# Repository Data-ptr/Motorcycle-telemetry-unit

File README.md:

# Motorcycle-Telemetry-Unit
 MTU

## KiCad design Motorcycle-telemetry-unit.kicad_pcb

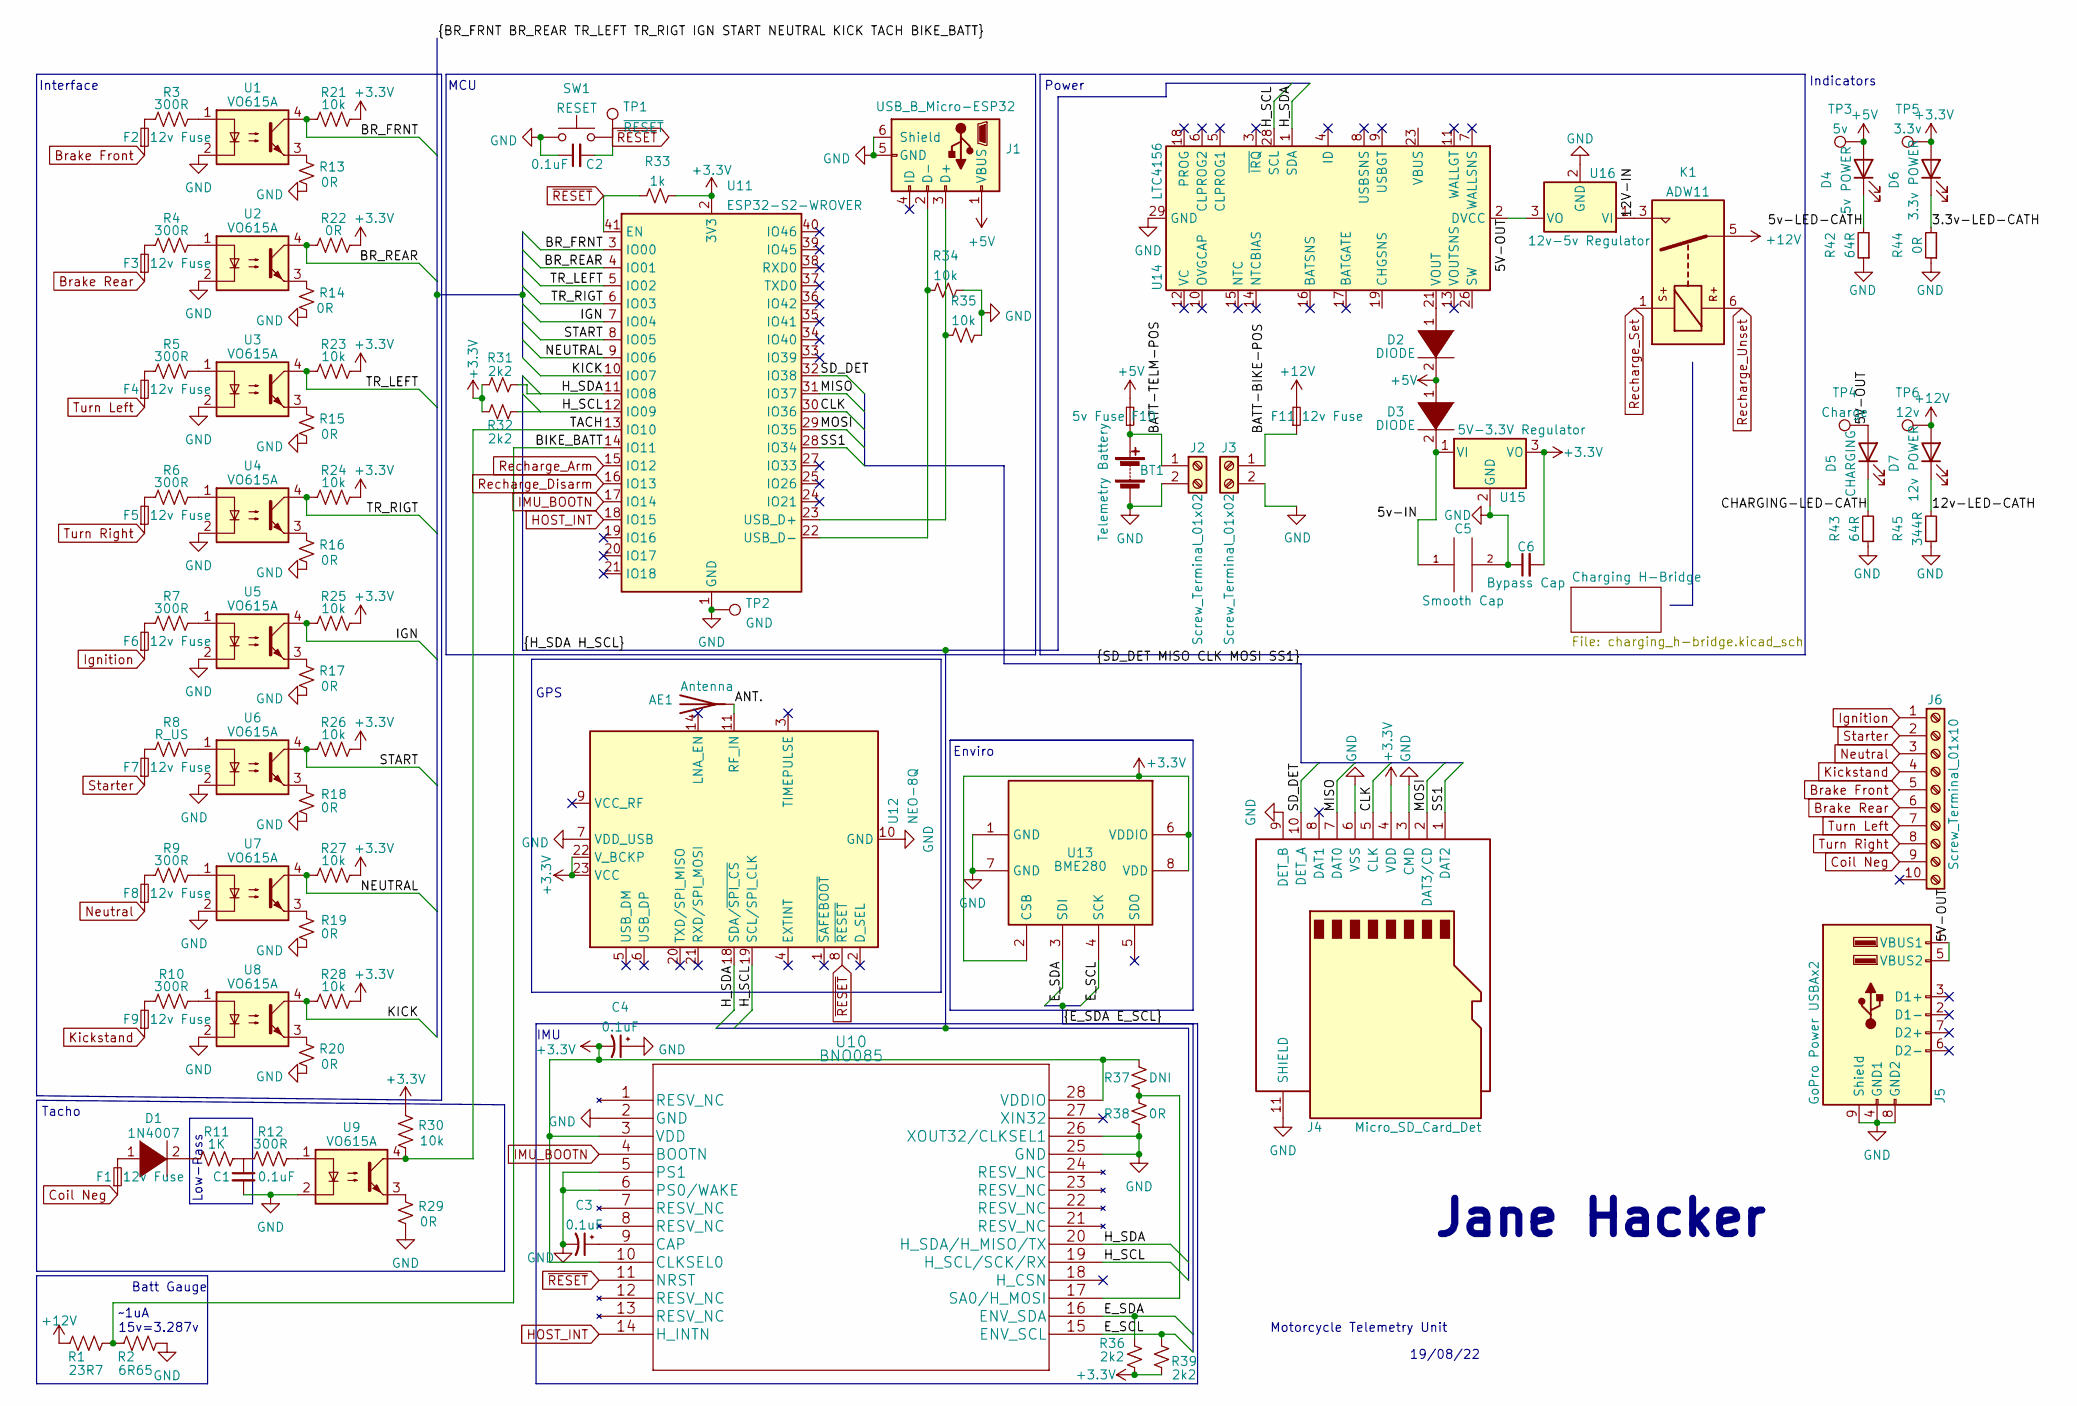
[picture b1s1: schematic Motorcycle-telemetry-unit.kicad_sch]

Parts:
AE1: Antenna; Texas_SWRA117D_2.4GHz_Right
BT1: Telemetry Battery; AMASS_XT60-M_1x02_P7.20mm_Vertical
C1, C2, C3, C4: 0.1uF; C_1206_3216Metric
C5: Smooth Cap; CP_Radial_D4.0mm_P1.50mm
C6: Bypass Cap; C_Disc_D3.0mm_W1.6mm_P2.50mm
D1: 1N4007; D_DO-35_SOD27_P7.62mm_Horizontal
D2, D3: DIODE; D_DO-35_SOD27_P7.62mm_Horizontal
D4: 5v POWER; LED_1206_3216Metric
D5: CHARGING; LED_1206_3216Metric
D6: 3.3v POWER; LED_1206_3216Metric
D7: 12v POWER; LED_1206_3216Metric
F1, F2, F3, F4, F5, F6, F7, F8, F9, F11: 12v Fuse; FUSE_BK-6013
F10: 5v Fuse; FUSE_BK-6013
J1: USB_B_Micro-ESP32; USB_Micro-B_Wuerth_629105150521
J2, J3: Screw_Terminal_01x02; TerminalBlock_Altech_AK300-2_P5.00mm
J4: Micro_SD_Card_Det; microSD_HC_Wuerth_693072010801
J5: GoPro Power USBAx2; USB_A_Wuerth_61400826021_Horizontal_Stacked
J6: Screw_Terminal_01x10; TerminalBlock_Phoenix_PT-1,5-10-5.0-H_1x10_P5.00mm_Horizont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
K1: ADW11; Relay_1P1T_NO_10x24x18.8mm_Panasonic_ADW11xxxxW_THT
R1: 23R7; R_1206_3216Metric
R2: 6R65; R_1206_3216Metric
R3, R4, R5, R6, R7, R9, R10, R12: 300R; R_1206_3216Metric
R8: R_US; R_1206_3216Metric
R11: 1K; R_1206_3216Metric
R13, R14, R15, R16, R17, R18, R19, R20, R22, R29, R38, R44: 0R; R_1206_3216Metric
R21, R23, R24, R25, R26, R27, R28, R30, R34, R35: 10k; R_1206_3216Metric
R31, R32, R36, R39: 2k2; R_1206_3216Metric
R33: 1k; R_1206_3216Metric
R37: DNI; R_1206_3216Metric
R42, R43: 64R; R_1206_3216Metric
R45: 344R; R_1206_3216Metric
SW1: RESET; SW_Push_1P1T_NO_6x6mm_H9.5mm
TP1: ~{RESET}; TestPoint_Loop_D2.50mm_Drill1.0mm
TP2: GND; TestPoint_Bridge_Pitch2.0mm_Drill0.7mm
TP3: 5v; TestPoint_Loop_D2.50mm_Drill1.0mm
TP4: Charge; TestPoint_Loop_D2.50mm_Drill1.0mm
TP5: 3.3v; TestPoint_Loop_D2.50mm_Drill1.0mm
TP6: 12v; TestPoint_Loop_D2.50mm_Drill1.0mm
U1, U2, U3, U4, U5, U6, U7, U8, U9: VO615A; DIP762W50P254L458H480Q4
U10: BNO085; LGA-28_5.2x3.8mm_P0.5mm
U11: ESP32-S2-WROVER
U12: NEO-8Q; ublox_NEO
U13: BME280; Bosch_LGA-8_2.5x2.5mm_P0.65mm_ClockwisePinNumbering
U14: LTC4156; QFN-28-1EP_4x5mm_P0.5mm_EP2.65x3.65mm
U15: 5V-3.3V Regulator; TO-252-2
U16: 12v-5v Regulator; TO-252-2

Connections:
+3V3: C4.2, C6.2, D6.2 (A), J4.4 (VDD), R21.2, R22.2, R23.2, R24.2, R25.2, R26.2, R27.2, R28.2, R30.2, R31.1, R32.1, R33.2, R36.1, R37.1, R39.1, TP5.1, U10.3 (VDD), U10.10 (CLKSEL0), U10.28 (VDDIO), U11.2 (3V3), U12.22 (V_BCKP), U12.23 (VCC), U13.2 (CSB), U13.6 (VDDIO), U13.8 (VDD), U15.3 (VO); also elsewhere on the board
+5V: D2.2 (A), D3.1 (K), D4.2 (A), F10.2, J1.1 (VBUS), TP3.1
+12V: D7.2 (A), F11.2, K1.5, R1.1, TP6.1
/3.3v-LED-CATH: D6.1 (K), R44.2
/5V-OUT: D5.2 (A), J5.1 (VBUS1), J5.5 (VBUS2), TP4.1, U14.2 (DVCC), U16.3 (VO)
/5v-IN: C5.1, D3.2 (A), U15.1 (VI)
/5v-LED-CATH: D4.1 (K), R42.2
/12V-IN: K1.3, U16.1 (VI)
/12v-LED-CATH: D7.1 (K), R45.2
/ANT.: AE1.1 (A), U12.11 (RF_IN)
/BATT-BIKE-POS: F11.1, J3.1
/BATT-TELM-POS: BT1.1 (+), F10.1, J2.1
/BIKE_BATT: R1.2, R2.1, U11.14 (IO11)
/BR_FRNT: R21.1, U1.4, U11.3 (IO00)
/BR_REAR: R22.1, U2.4, U11.4 (IO01)
/CHARGING-LED-CATH: D5.1 (K), R43.2
/CLK: J4.5 (CLK), U11.30 (IO36)
/E_SCL: R39.2, U10.15 (ENV_SCL), U13.4 (SCK)
/E_SDA: R36.2, U10.16 (ENV_SDA), U13.3 (SDI)
/H_SCL: R32.2, U10.19 (H_SCL/SCK/RX), U11.12 (IO09), U12.19 (SCL/SPI_CLK), U14.28 (SCL)
/H_SDA: R31.2, U10.20 (H_SDA/H_MISO/TX), U11.11 (IO08), U12.18 (SDA/~SPI_CS), U14.1 (SDA)
/IGN: R25.1, U5.4, U11.7 (IO04)
/KICK: R28.1, U8.4, U11.10 (IO07)
/MISO: J4.7 (DAT0), U11.31 (IO37)
/MOSI: J4.2 (DAT3/CD), U11.29 (IO35)
/NEUTRAL: R27.1, U7.4, U11.9 (IO06)
/SD_DET: J4.10 (DET_A), U11.32 (IO38)
/SS1: J4.1 (DAT2), U11.28 (IO34)
/START: R26.1, U6.4, U11.8 (IO05)
/TACH: R30.1, U9.4, U11.13 (IO10)
/TR_LEFT: R23.1, U3.4, U11.5 (IO02)
/TR_RIGT: R24.1, U4.4, U11.6 (IO03)
Brake Front: F2.1, J6.5
Brake Rear: F3.1, J6.6
Coil Neg: F1.1, J6.9
GND: BT1.2 (-), C1.2, C2.1, C3.2, C4.1, C5.2, C6.1, J1.5 (GND), J1.6 (Shield), J2.2, J3.2, J4.3 (CMD), J4.6 (VSS), J4.9 (DET_B), J4.11 (SHIELD), J5.4 (GND1), J5.8 (GND2), J5.9 (Shield), R2.2, R13.2, R14.2, R15.2, R16.2, R17.2, R18.2, R19.2, R20.2, R29.2, R34.2, R35.2, R38.2, R42.1, R43.1, R44.1, R45.1, SW1.1, TP2.1, U1.2, U2.2, U3.2, U4.2, U5.2, U6.2, U7.2, U8.2, U9.2, U10.2 (GND), U10.5 (PS1), U10.6 (PS0/WAKE), U10.25 (GND), U10.26 (XOUT32/CLKSEL1), U11.1 (GND), U11.26 (GND), U11.42 (GND), U11.43 (GND), U12.7 (VDD_USB), U12.10 (GND), U12.12 (GND), U12.13 (GND), U12.24 (GND), U13.1 (GND), U13.7 (GND), U14.29 (GND), U15.2 (GND), U16.2 (GND); also elsewhere on the board
HOST_INT: U10.14 (H_INTN), U11.18 (IO15)
IMU_BOOTN: U10.4 (BOOTN), U11.17 (IO14)
Ignition: F6.1, J6.1
Kickstand: F9.1, J6.4
unnamed: C1.1, R11.2, R12.1
unnamed: C3.1, U10.9 (CAP)
unnamed: D1.1 (K), F1.2
unnamed: D1.2 (A), R11.1
unnamed: D2.1 (K), U14.21 (VOUT), U14.22 (VOUT)
unnamed: F2.2, R3.1
unnamed: F3.2, R4.1
unnamed: F4.2, R5.1
unnamed: F5.2, R6.1
unnamed: F6.2, R7.1
unnamed: F7.2, R8.1
unnamed: F8.2, R9.1
unnamed: F9.2, R10.1
unnamed: J1.2 (D-), R34.1, U11.22 (USB_D-)
unnamed: J1.3 (D+), R35.1, U11.23 (USB_D+)
unnamed: R3.2, U1.1
unnamed: R4.2, U2.1
unnamed: R5.2, U3.1
unnamed: R6.2, U4.1
unnamed: R7.2, U5.1
unnamed: R8.2, U6.1
unnamed: R9.2, U7.1
unnamed: R10.2, U8.1
unnamed: R12.2, U9.1
unnamed: R13.1, U1.3
unnamed: R14.1, U2.3
unnamed: R15.1, U3.3
unnamed: R16.1, U4.3
unnamed: R17.1, U5.3
unnamed: R18.1, U6.3
unnamed: R19.1, U7.3
unnamed: R20.1, U8.3
unnamed: R29.1, U9.3
unnamed: R37.2, R38.1, U10.17 (SA0/H_MOSI)
unnamed: U14.19 (CHGSNS), U14.20 (CHGSNS)
unnamed: U14.23 (VBUS), U14.24 (VBUS), U14.25 (VBUS)
unnamed: U14.26 (SW), U14.27 (SW)
Neutral: F8.1, J6.3
Recharge_Arm: U11.15 (IO12); also elsewhere on the board
Recharge_Disarm: U11.16 (IO13); also elsewhere on the board
Recharge_Set: K1.1; also elsewhere on the board
Recharge_Unset: K1.6; also elsewhere on the board
Starter: F7.1, J6.2
Turn Left: F4.1, J6.7
Turn Right: F5.1, J6.8
~RESET: C2.2, R33.1, SW1.2, TP1.1, U10.11 (NRST), U11.41 (EN), U12.8 (~RESET)

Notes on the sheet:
MCU
Jane Hacker
Low-Pass
Interface
Power
Motorcycle Telemetry Unit
19/08/22
GPS
Enviro
Batt Gauge
Indicators
~1uA 15v=3.287v
IMU
Tacho

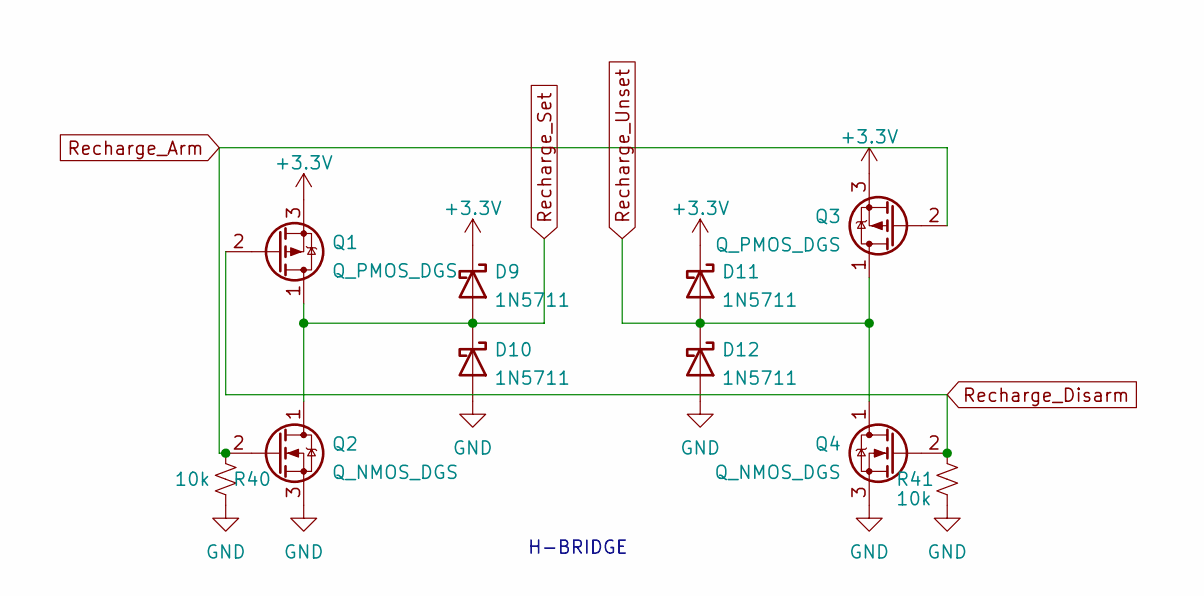
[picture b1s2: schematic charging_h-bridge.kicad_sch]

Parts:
D9, D10, D11, D12: 1N5711; D_DO-35_SOD27_P7.62mm_Horizontal
Q1, Q3: Q_PMOS_DGS; TO-220-3_Vertical
Q2, Q4: Q_NMOS_DGS; TO-220-3_Vertical
R40, R41: 10k; R_1206_3216Metric

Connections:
+3V3: D9.1 (K), D11.1 (K), Q1.3 (S), Q3.3 (S); also elsewhere on the board
GND: D10.2 (A), D12.2 (A), Q2.3 (S), Q4.3 (S), R40.1, R41.2; also elsewhere on the board
Recharge_Arm: Q2.2 (G), Q3.2 (G), R40.2; also elsewhere on the board
Recharge_Disarm: Q1.2 (G), Q4.2 (G), R41.1; also elsewhere on the board
Recharge_Set: D9.2 (A), D10.1 (K), Q1.1 (D), Q2.1 (D); also elsewhere on the board
Recharge_Unset: D11.2 (A), D12.1 (K), Q3.1 (D), Q4.1 (D); also elsewhere on the board

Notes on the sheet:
H-BRIDGE

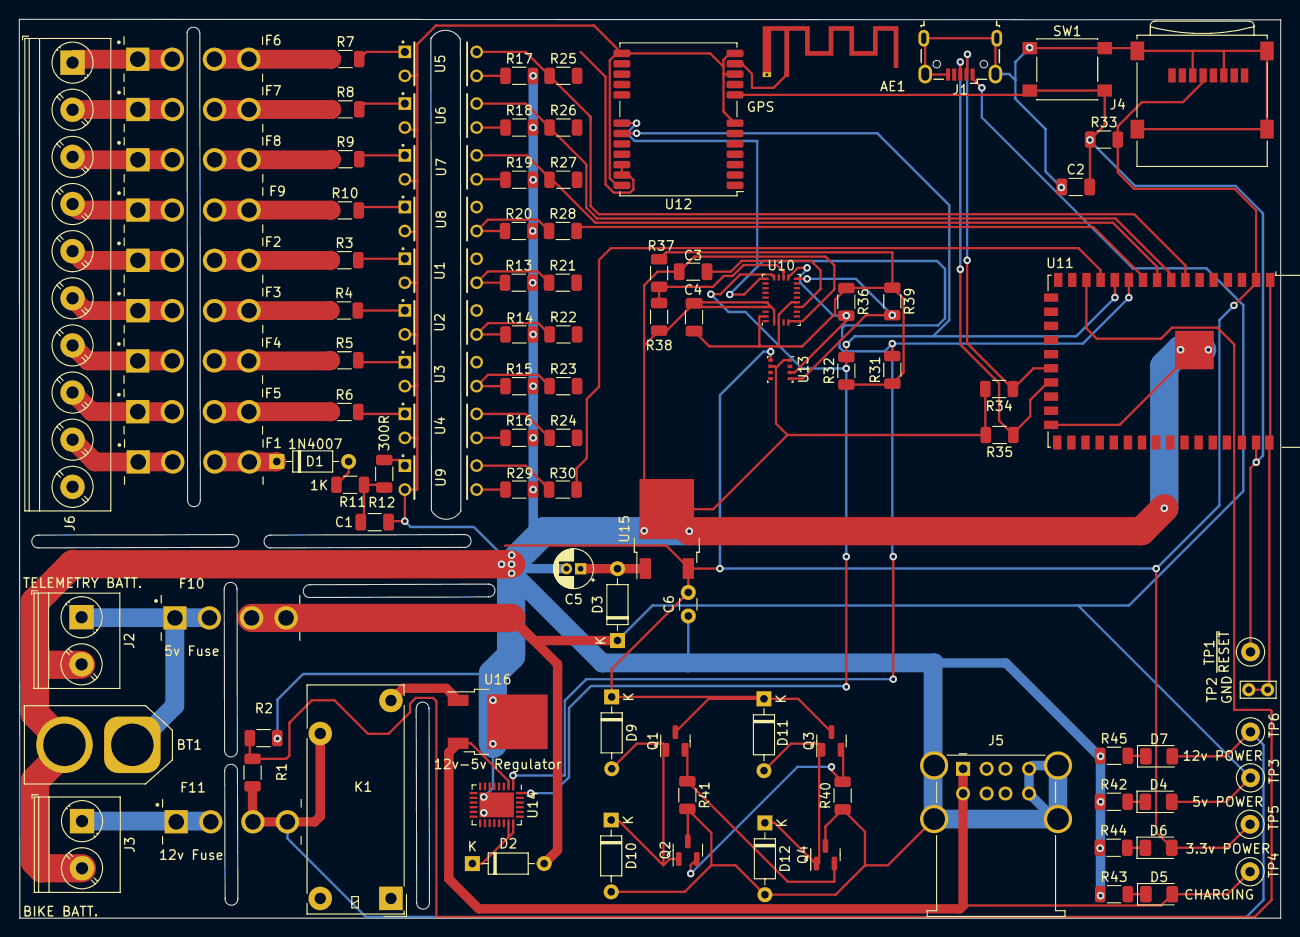
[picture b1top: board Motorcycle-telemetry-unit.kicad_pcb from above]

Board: 2 copper layers, 133.8 x 95.4 mm, 109 parts (0 on the bottom side), 85 nets.

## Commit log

2022-08-25 Including library imports
2022-08-25 Fixes and updates
2022-08-25 Update Motorcycle-telemetry-unit.kicad_pcb
    Wiring
2022-08-25 More clean up
2022-08-26 wired
2022-08-26 Corrections to optoarray
